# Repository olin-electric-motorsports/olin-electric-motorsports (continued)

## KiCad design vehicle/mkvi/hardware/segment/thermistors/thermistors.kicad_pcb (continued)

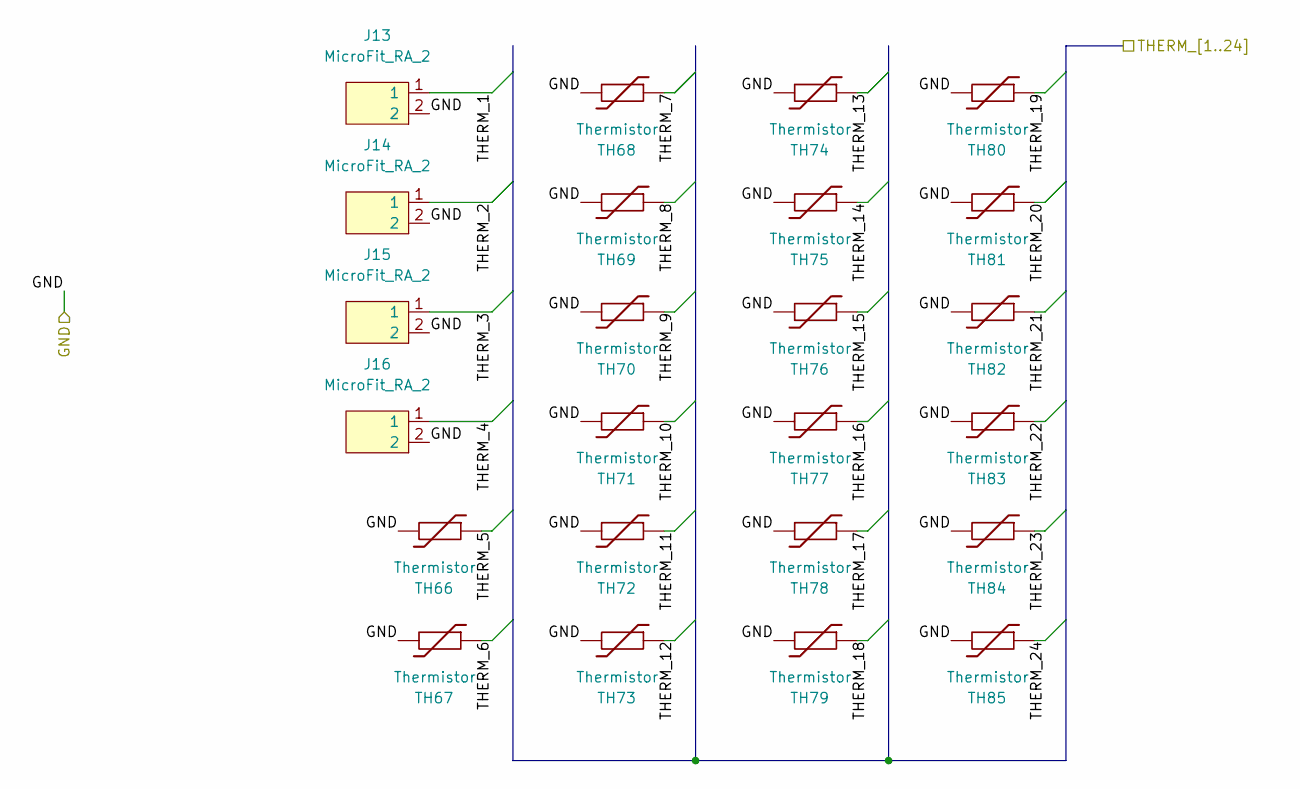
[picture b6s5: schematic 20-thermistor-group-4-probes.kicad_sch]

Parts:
J13, J14, J15, J16: MicroFit_RA_2; MPN 0436500201
TH66, TH67, TH68, TH69, TH70, TH71, TH72, TH73, TH74, TH75, TH76, TH77, TH78, TH79, TH80, TH81, TH82, TH83, TH84, TH85: Thermistor; R_0603; MPN 273-TX06F104F4100ERDKR-ND

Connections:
/20-4/THERM_1: J13.1; also elsewhere on the board
/20-4/THERM_2: J14.1; also elsewhere on the board
/20-4/THERM_3: J15.1; also elsewhere on the board
/20-4/THERM_4: J16.1; also elsewhere on the board
/20-4/THERM_5: TH66.1; also elsewhere on the board
/20-4/THERM_6: TH67.1; also elsewhere on the board
/20-4/THERM_7: TH68.1; also elsewhere on the board
/20-4/THERM_8: TH69.1; also elsewhere on the board
/20-4/THERM_9: TH70.1; also elsewhere on the board
/20-4/THERM_10: TH71.1; also elsewhere on the board
/20-4/THERM_11: TH72.1; also elsewhere on the board
/20-4/THERM_12: TH73.1; also elsewhere on the board
/20-4/THERM_13: TH74.1; also elsewhere on the board
/20-4/THERM_14: TH75.1; also elsewhere on the board
/20-4/THERM_15: TH76.1; also elsewhere on the board
/20-4/THERM_16: TH77.1; also elsewhere on the board
/20-4/THERM_17: TH78.1; also elsewhere on the board
/20-4/THERM_18: TH79.1; also elsewhere on the board
/20-4/THERM_19: TH80.1; also elsewhere on the board
/20-4/THERM_20: TH81.1; also elsewhere on the board
/20-4/THERM_21: TH82.1; also elsewhere on the board
/20-4/THERM_22: TH83.1; also elsewhere on the board
/20-4/THERM_23: TH84.1; also elsewhere on the board
/20-4/THERM_24: TH85.1; also elsewhere on the board
/GND: J13.2, J14.2, J15.2, J16.2, TH66.2, TH67.2, TH68.2, TH69.2, TH70.2, TH71.2, TH72.2, TH73.2, TH74.2, TH75.2, TH76.2, TH77.2, TH78.2, TH79.2, TH80.2, TH81.2, TH82.2, TH83.2, TH84.2, TH85.2; also elsewhere on the board

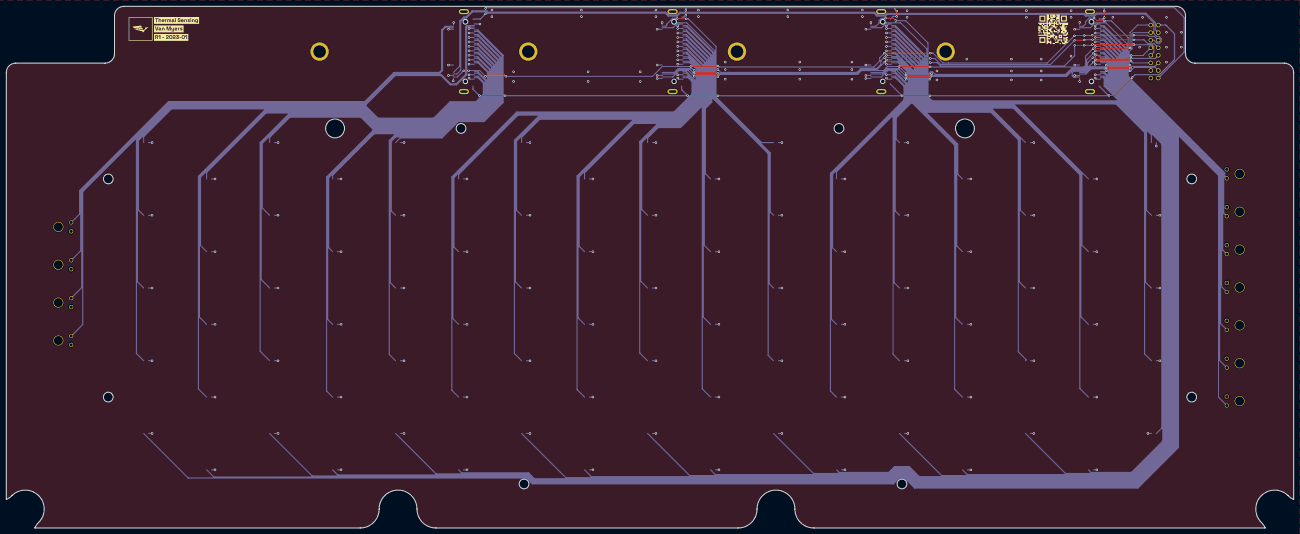
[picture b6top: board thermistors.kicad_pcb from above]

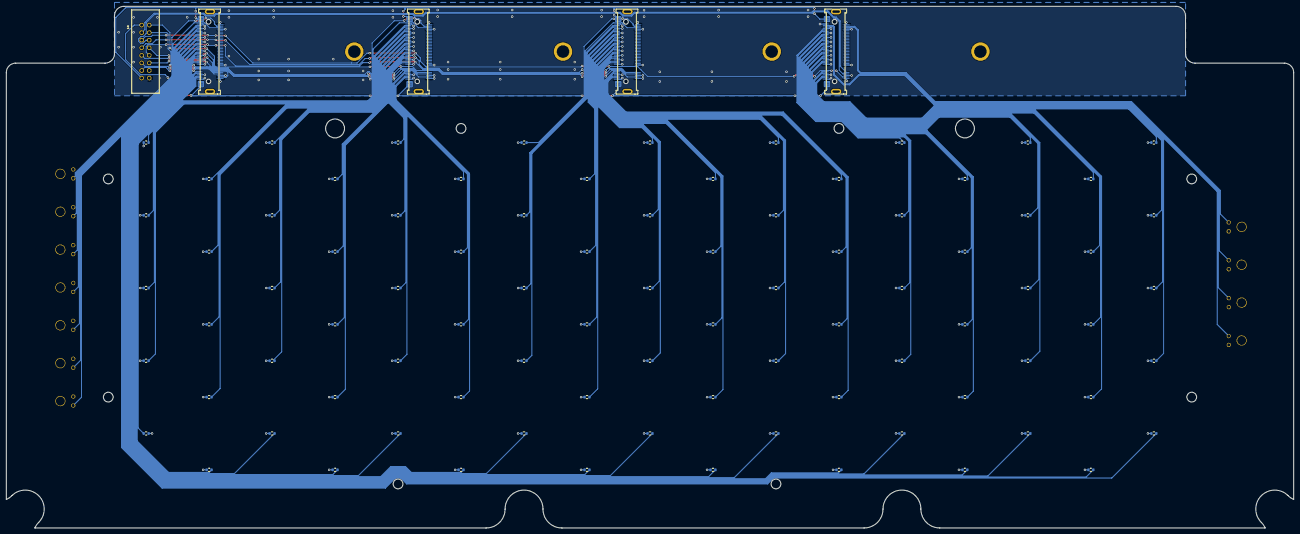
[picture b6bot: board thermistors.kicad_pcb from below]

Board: 2 copper layers, 431.8 x 175.0 mm, 105 parts (101 on the bottom side), 111 nets.

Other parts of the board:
J3, J4, J5: Automotive_M.2; MKVI_DA_Module
QR*****: hw.oem.to/6_THERMAL_1; QR_6_THERMAL_1
kibuzzard-63B8B2B4: G***; kibuzzard-63B8B2B4
kibuzzard-63B8B2E9: G***; kibuzzard-63B8B2E9
kibuzzard-63BC82F4: G***; kibuzzard-63BC82F4

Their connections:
/20-4/THERM_1: J5.72; also elsewhere on the board
/20-4/THERM_2: J5.71; also elsewhere on the board
/20-4/THERM_3: J5.36; also elsewhere on the board
/20-4/THERM_4: J5.35; also elsewhere on the board
/20-4/THERM_5: J5.33; also elsewhere on the board
/20-4/THERM_6: J5.32; also elsewhere on the board
/20-4/THERM_7: J5.30; also elsewhere on the board
/20-4/THERM_8: J5.29; also elsewhere on the board
/20-4/THERM_9: J5.27; also elsewhere on the board
/20-4/THERM_10: J5.26; also elsewhere on the board
/20-4/THERM_11: J5.24; also elsewhere on the board
/20-4/THERM_12: J5.23; also elsewhere on the board
/20-4/THERM_13: J5.21; also elsewhere on the board
/20-4/THERM_14: J5.20; also elsewhere on the board
/20-4/THERM_15: J5.18; also elsewhere on the board
/20-4/THERM_16: J5.17; also elsewhere on the board
/20-4/THERM_17: J5.15; also elsewhere on the board
/20-4/THERM_18: J5.14; also elsewhere on the board
/20-4/THERM_19: J5.12; also elsewhere on the board
/20-4/THERM_20: J5.11; also elsewhere on the board
/20-4/THERM_21: J5.9; also elsewhere on the board
/20-4/THERM_22: J5.8; also elsewhere on the board
/20-4/THERM_23: J5.6; also elsewhere on the board
/20-4/THERM_24: J5.5; also elsewhere on the board
/24x1/THERM_1: J3.72; also elsewhere on the board
/24x1/THERM_2: J3.71; also elsewhere on the board
/24x1/THERM_3: J3.36; also elsewhere on the board
/24x1/THERM_4: J3.35; also elsewhere on the board
/24x1/THERM_5: J3.33; also elsewhere on the board
/24x1/THERM_6: J3.32; also elsewhere on the board
/24x1/THERM_7: J3.30; also elsewhere on the board
/24x1/THERM_8: J3.29; also elsewhere on the board
/24x1/THERM_9: J3.27; also elsewhere on the board
/24x1/THERM_10: J3.26; also elsewhere on the board
/24x1/THERM_11: J3.24; also elsewhere on the board
/24x1/THERM_12: J3.23; also elsewhere on the board
/24x1/THERM_13: J3.21; also elsewhere on the board
/24x1/THERM_14: J3.20; also elsewhere on the board
/24x1/THERM_15: J3.18; also elsewhere on the board
/24x1/THERM_16: J3.17; also elsewhere on the board
/24x1/THERM_17: J3.15; also elsewhere on the board
/24x1/THERM_18: J3.14; also elsewhere on the board
/24x1/THERM_19: J3.12; also elsewhere on the board
/24x1/THERM_20: J3.11; also elsewhere on the board
/24x1/THERM_21: J3.9; also elsewhere on the board
/24x1/THERM_22: J3.8; also elsewhere on the board
/24x1/THERM_23: J3.6; also elsewhere on the board
/24x1/THERM_24: J3.5; also elsewhere on the board
/24x2/THERM_1: J4.72; also elsewhere on the board
/24x2/THERM_2: J4.71; also elsewhere on the board
/24x2/THERM_3: J4.36; also elsewhere on the board
/24x2/THERM_4: J4.35; also elsewhere on the board
/24x2/THERM_5: J4.33; also elsewhere on the board
/24x2/THERM_6: J4.32; also elsewhere on the board
/24x2/THERM_7: J4.30; also elsewhere on the board
/24x2/THERM_8: J4.29; also elsewhere on the board
/24x2/THERM_9: J4.27; also elsewhere on the board
/24x2/THERM_10: J4.26; also elsewhere on the board
/24x2/THERM_11: J4.24; also elsewhere on the board
/24x2/THERM_12: J4.23; also elsewhere on the board
/24x2/THERM_13: J4.21; also elsewhere on the board
/24x2/THERM_14: J4.20; also elsewhere on the board
/24x2/THERM_15: J4.18; also elsewhere on the board
/24x2/THERM_16: J4.17; also elsewhere on the board
/24x2/THERM_17: J4.15; also elsewhere on the board
/24x2/THERM_18: J4.14; also elsewhere on the board
/24x2/THERM_19: J4.12; also elsewhere on the board
/24x2/THERM_20: J4.11; also elsewhere on the board
/24x2/THERM_21: J4.9; also elsewhere on the board
/24x2/THERM_22: J4.8; also elsewhere on the board
/24x2/THERM_23: J4.6; also elsewhere on the board
/24x2/THERM_24: J4.5; also elsewhere on the board
/GND: J3.4, J3.7, J3.10, J3.13, J3.16, J3.19, J3.22, J3.25, J3.28, J3.31, J3.34, J3.37, J3.41, J3.43, J3.46, J3.70, J3.73, J4.4, J4.7, J4.10, J4.13, J4.16, J4.19, J4.22, J4.25, J4.28, J4.31, J4.34, J4.37, J4.41, J4.43, J4.46, J4.70, J4.73, J5.4, J5.7, J5.10, J5.13, J5.16, J5.19, J5.22, J5.25, J5.28, J5.31, J5.34, J5.37, J5.41, J5.43, J5.46, J5.70, J5.73; also elsewhere on the board
/MUX2_SC: J3.44; also elsewhere on the board
/MUX2_SD: J3.45; also elsewhere on the board
/MUX3_SC: J4.44; also elsewhere on the board
/MUX3_SD: J4.45; also elsewhere on the board
/MUX4_SC: J5.44; also elsewhere on the board
/MUX4_SD: J5.45; also elsewhere on the board
/MUX_OUT_2: J3.42; also elsewhere on the board
/MUX_OUT_3: J4.42; also elsewhere on the board
/MUX_OUT_4: J5.42; also elsewhere on the board
/VREF2: J3.P38, J3.P39, J3.P40, J4.P38, J4.P39, J4.P40, J5.P38, J5.P39, J5.P40; also elsewhere on the board
/VREG: J3.P1, J3.P2, J3.P3, J4.P1, J4.P2, J4.P3, J5.P1, J5.P2, J5.P3; also elsewhere on the board

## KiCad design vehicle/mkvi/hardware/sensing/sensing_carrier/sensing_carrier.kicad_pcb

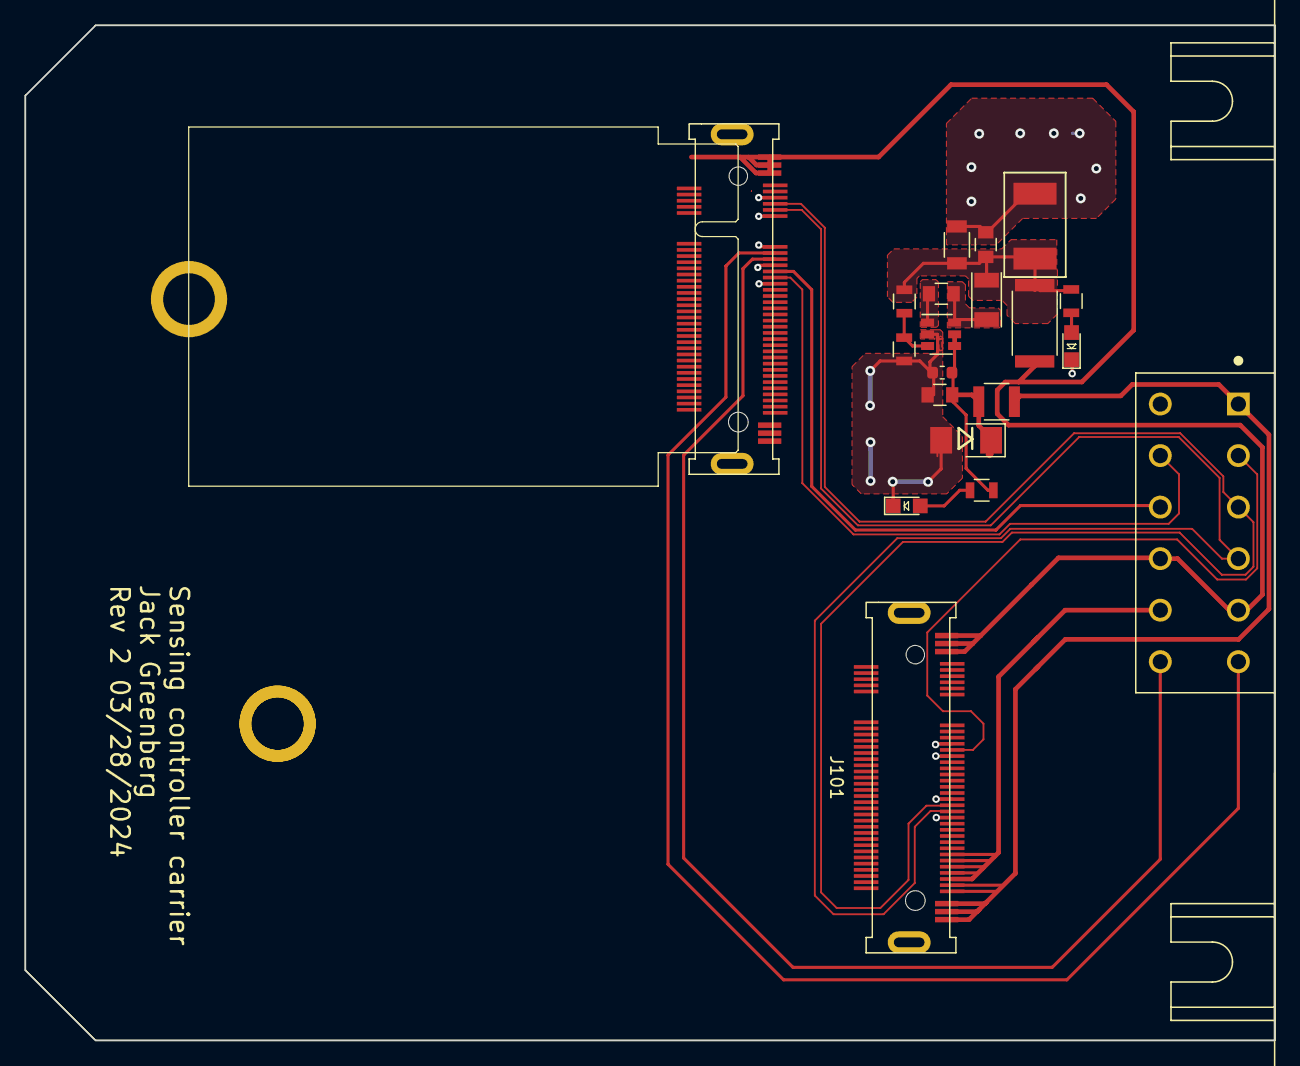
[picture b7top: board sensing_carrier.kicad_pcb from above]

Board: 2 copper layers, 101.6 x 82.5 mm, 20 parts (0 on the bottom side), 18 nets.

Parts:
C101, C103: C_0.1uF; C_0805_OEM
C102: C_2.2uF; C_0603_1608Metric
COUT101: C_22uF; C_1206_OEM
COUT102: C_33uF; Fuse_1812
COUT103: C_47uF; C_0805_OEM
D101: D_Zener_18V; DO-214AA
D102, D103: LED_0805; LED_0805_OEM
F101: F_500mA_16V; Fuse_1210
J1: Conn_02x06_Counter_Clockwise; TE_DTM13-12PA-R008
J2, J101: Automotive_M.2
L101: L_100uH; L_100uH_OEM
R101: R_1K; R_0805_OEM
R102: R_25K; R_0805_OEM
R103: R_100K; R_0805_OEM
R104: R_0_2512; R_2512_OEM
R105: R_200; R_0805_OEM
U101: TPS560430YF; SOT-23-6_OEM

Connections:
+5V: J1.5, J1.9, J2.P1, J2.P2, J2.P3, J101.P1, J101.P2, J101.P3, R104.1
+BATT: F101.2, J1.1, J101.36, J101.37, J101.P38, J101.P39, J101.P40
/CAN_N: J1.4, J2.8, J101.24
/CAN_P: J1.3, J2.7, J101.23
/FAN_POWER: J1.8, J101.31, J101.32, J101.33, J101.34, J101.35
/PUMP_SIGNAL: J1.2, J101.14
/SUS_POT_B_L_SIG: J1.10, J2.14
/SUS_POT_B_R_SIG: J1.11, J2.15
/WS_B_L_SIG: J1.6, J2.11
/WS_B_R_SIG: J1.7, J2.12
GND: C101.2, C102.2, COUT101.2, COUT102.2, COUT103.2, D101.2 (A), D102.1 (K), D103.1 (K), J1.12, J2.6, J2.9, J2.10, J2.13, J2.16, J101.13, J101.15, J101.22, J101.25, R102.2, U101.2 (GND)
unnamed: COUT101.1, COUT102.1, COUT103.1, L101.2, R103.1, R104.2, R105.1
unnamed: C101.1, C102.1, D101.1 (K), F101.1, R101.1, U101.4 (EN), U101.5 (VIN)
unnamed: D102.2 (A), R101.2
unnamed: D103.2 (A), R105.2
unnamed: C103.1, U101.1 (CB)
unnamed: R102.1, R103.2, U101.3 (FB)
unnamed: C103.2, L101.1, U101.6 (SW)

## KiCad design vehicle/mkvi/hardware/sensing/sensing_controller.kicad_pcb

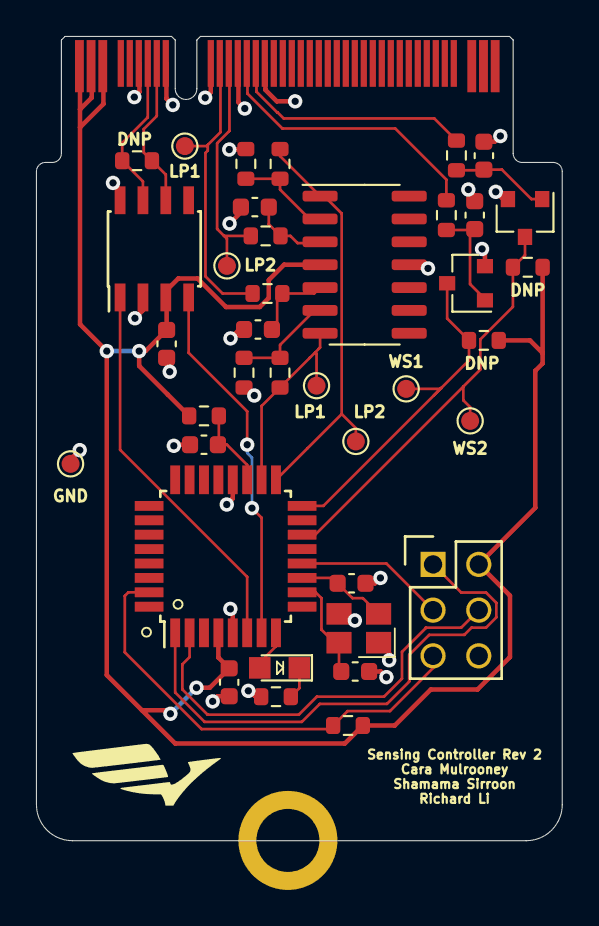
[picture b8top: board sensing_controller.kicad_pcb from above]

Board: 2 copper layers, 29.2 x 44.7 mm, 40 parts (0 on the bottom side), 29 nets.

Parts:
C1, C3, C6, C8: C_0.1uF; C_0603
C2: C_100pF; C_0603
C4, C5: C_30pF; C_0603
C9, C10: C_0uF; C_0603
D1: LED_0805; LED_0805_OEM
GND1: TestPoint; TestPoint_Pad_D1.0mm
J1: Automotive_M.2_Edge_Connector
J2: CONN_02X03; Pin_Header_Straight_2x03
LP1_POST1, LP1_PRE1, LP2_POST1, LP2_PRE1: TestPoint; TestPoint_Pad_D1.0mm
Q1, Q2: SSM3K333R; SOT-23F
R1, R4, R6, R7, R8, R14: R_100; R_0603
R2: R_120_DNP; R_0603
R3: R_10K; R_0603
R5, R11: R_200; R_0603
R9, R10: R_0; R_0603
R12, R13: R_1K_DNP; R_0603
U1: MCP2561-E_SN; SOIC-8_3.9x4.9mm_Pitch1.27mm_OEM
U2: ATMEGA16M1; TQFP-32_7x7mm_Pitch0.8mm
U4: AD8630; SOIC-14_3.9x8.7mm_P1.27mm
U$2: M.2_Mount
WS1, WS2: TestPoint; TestPoint_Pad_D1.0mm
Y1: Crystal_SMD; Crystal_SMD_FA238

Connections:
+5V: C1.1, C3.1, J1.P1, J1.P2, J1.P3, J2.2, R1.1, R3.1, R12.2, R13.2, U1.3 (VDD), U2.4 (VCC), U4.4 (V+)
/CAN_+: J1.7, R2.1, U1.7 (CANH)
/CAN_-: J1.8, R2.2, U1.6 (CANL)
/CAN_RX: U1.4 (RXD), U2.7 ((PCINT11/T1/ICP1B/RXCAN)PC3)
/CAN_TX: U1.1 (TXD), U2.6 ((PCINT10/T0/TXCAN)PC2)
/DEBUG_LED: D1.2 (A), U2.8 ((PCINT0/MISO/PSCOUT2A)PB0)
/MISO: J2.1, U2.1 ((PCINT18/PSCIN2/OC1A/MISO_A)PD2)
/MOSI: J2.4, U2.2 ((PCINT19/TXD/TXLIN/OC0A/~SS/MOSI_A)PD3)
/RESET: J2.5, R3.2, U2.31 ((PCINT24/OCD/~RESET)PE0)
/SCK: J2.3, U2.12 ((PCINT20/ADC1/RXD/RXLIN/ICP1A/SCK_A)PD4)
/lp1_Vout: J1.11, LP1_PRE1.1, R8.1
/lp1_fVout: LP1_POST1.1, R14.1, U2.18 ((PCINT13/ADC9/ACMP3/AMP1+)PC5), U4.7
/lp2_Vout: J1.12, LP2_PRE1.1, R7.1
/lp2_fVout: LP2_POST1.1, R6.1, U2.17 ((PCINT12/ADC8/ACMPN3/AMP1-)PC4), U4.1
/ws1_Vout: J1.14, R10.1
/ws1_fVout: Q2.3 (D), R13.1, U2.16 ((PCINT2/ADC5/INT1/ACMPN0)PB2), WS1.1
/ws2_Vout: J1.15, R9.1
/ws2_fVout: Q1.3 (D), R12.1, U2.14 ((PCINT22/ADC3/INT0/ACMPN2)PD6), WS2.1
GND: C1.2, C2.2, C3.2, C4.2, C5.2, C6.2, C8.2, C9.2, C10.2, GND1.1, J1.6, J1.9, J1.10, J1.13, J1.16, J2.6, Q1.2 (S), Q2.2 (S), R4.2, R5.1, R11.1, U1.2 (VSS), U1.8 (STBY), U2.5 (GND), U2.20 (AGND), U4.11 (V-), U$2.1, Y1.2, Y1.4
unnamed: C2.1, R1.2, U2.19 (AVCC)
unnamed: C4.1, U2.11 ((PCINT26/ADC0/XTAL2)PE2), Y1.1
unnamed: C5.1, U2.10 ((PCINT25/OC0B/XTAL1)PE1), Y1.3
unnamed: C6.1, R7.2, U4.3 (+)
unnamed: C8.1, R8.2, U4.5 (+)
unnamed: C9.1, Q1.1 (G), R9.2
unnamed: C10.1, Q2.1 (G), R10.2
unnamed: D1.1 (K), R4.1
unnamed: R5.2, R6.2, U4.2 (-)
unnamed: R11.2, R14.2, U4.6 (-)
